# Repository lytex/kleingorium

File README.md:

# Power specs
VCC to GND voltage: 5V to 18V
# Scales generated by it
[kleingorium scale](https://sevish.com/scaleworkshop/?n=kleingorium&l=2F8_3F8_4F8_5F8_6F8_8Fa_7F8_8F9_8F8_9F8_8F7_aF8_8F6_8F5_8F4_8F3_8F2&c=-~~~~~-~-~~-~----&d=6&y=46&version=2.5.7)

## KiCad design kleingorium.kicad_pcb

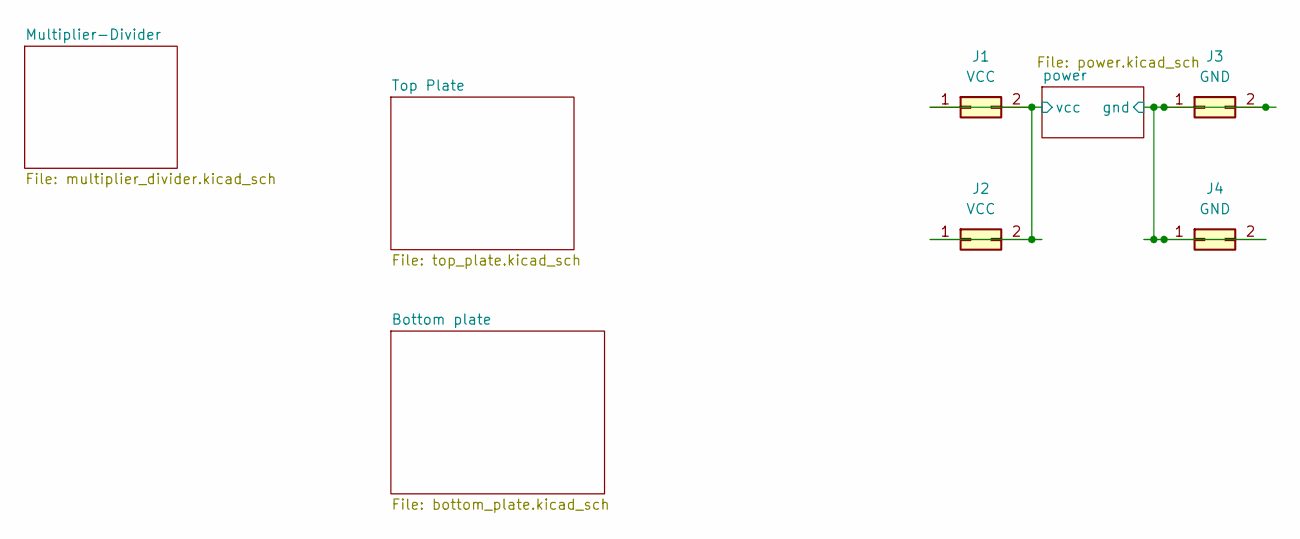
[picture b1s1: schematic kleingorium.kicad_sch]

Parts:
J1, J2: VCC; PinHeader_2x01_P2.54mm_Vertical
J3, J4: GND; PinHeader_2x01_P2.54mm_Vertical

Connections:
GND: J3.1, J3.2, J4.1, J4.2; also elsewhere on the board
VCC: J1.1, J1.2, J2.1, J2.2; also elsewhere on the board

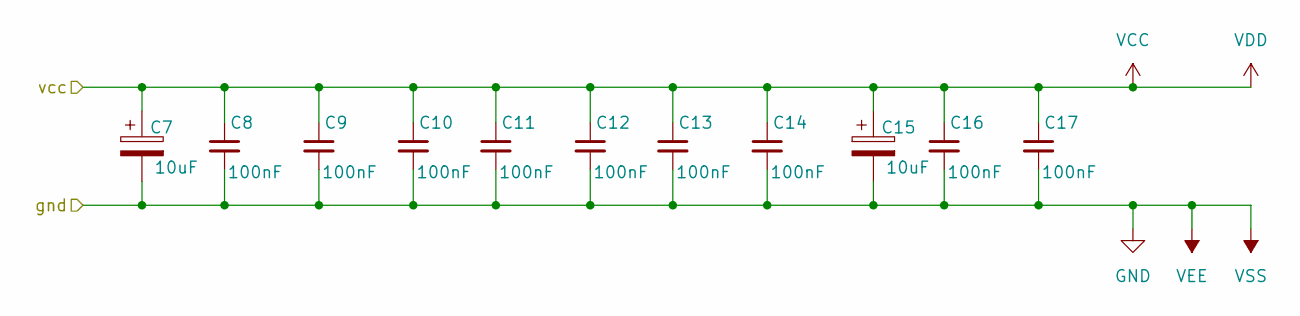
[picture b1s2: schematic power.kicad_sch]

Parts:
C7, C15: 10uF; CP_Radial_D10.0mm_P2.50mm
C8, C9, C10, C11, C12, C13, C14, C16, C17: 100nF; C_0805_2012Metric

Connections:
GND: C7.2, C8.2, C9.2, C10.2, C11.2, C12.2, C13.2, C14.2, C15.2, C16.2, C17.2; also elsewhere on the board
VCC: C7.1, C8.1, C9.1, C10.1, C11.1, C12.1, C13.1, C14.1, C15.1, C16.1, C17.1; also elsewhere on the board

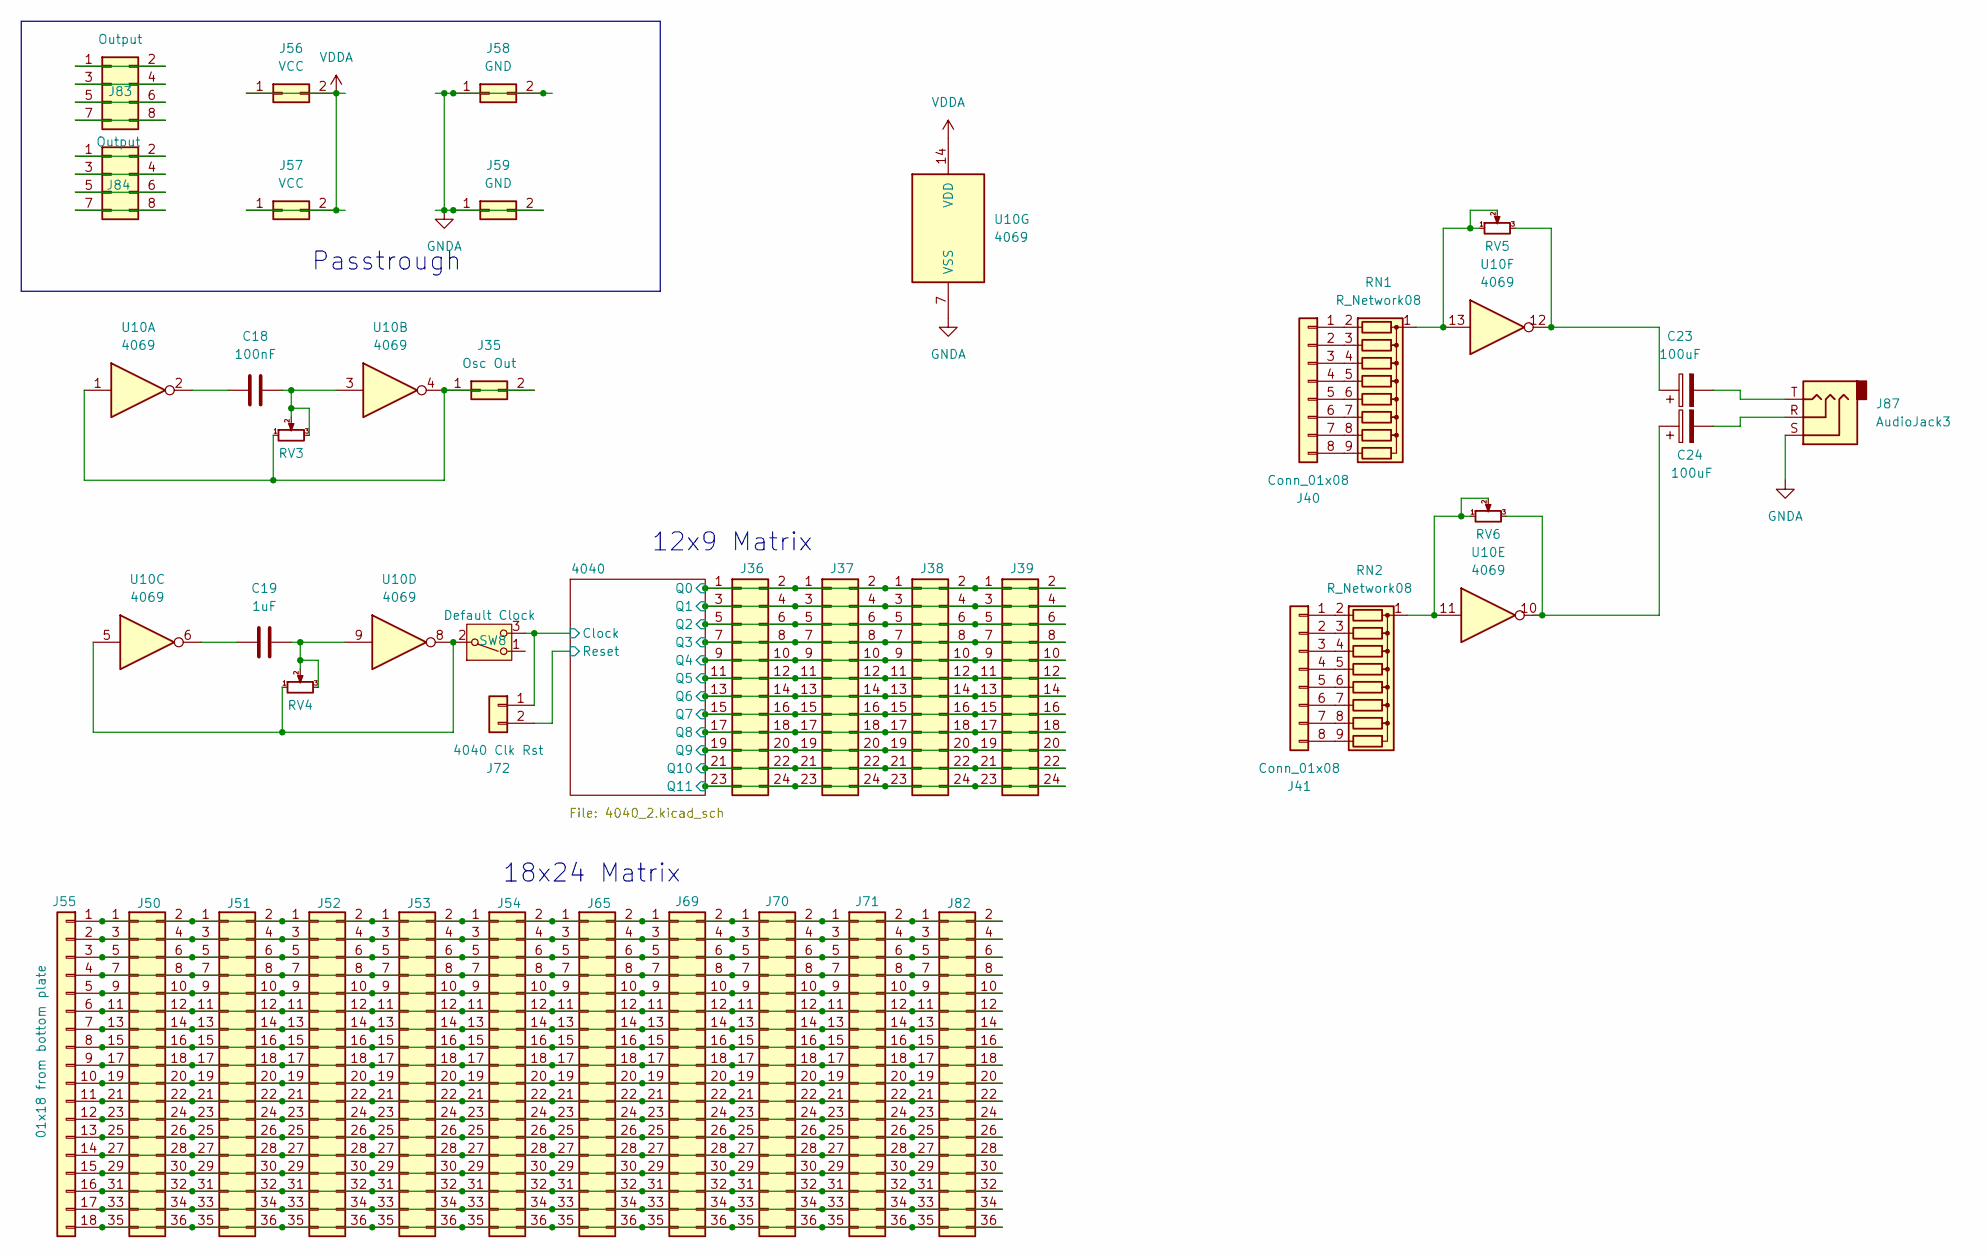
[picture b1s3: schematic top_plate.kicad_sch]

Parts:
C18: 100nF; C_0805_2012Metric
C19: 1uF; C_0805_2012Metric
C23, C24: 100uF; CP_Radial_D10.0mm_P2.50mm
J35: Osc Out; PinHeader_2x01_P2.54mm_Vertical
J36, J37, J38, J39: Conn_02x12_Odd_Even; Header_2x12_P2.54mm_Vertical_SMD_FH-00369
J40, J41: Conn_01x08; PinSocket_1x08_P2.54mm_Vertical
J50, J51, J52, J53, J54, J65, J69, J70, J71, J82: Conn_02x18_Odd_Even; Header_2x18_P2.54mm_Vertical_SMD_FH-00369
J55: 01x18 from bottom plate; PinHeader_1x18_P2.54mm_Vertical
J56, J57: VCC; PinHeader_2x01_P2.54mm_Vertical
J58, J59: GND; PinHeader_2x01_P2.54mm_Vertical
J72: 4040 Clk Rst; PinHeader_1x02_P2.54mm_Vertical
J83, J84: Output; PinHeader_2x04_P2.54mm_Vertical
J87: AudioJack3; Jack_3.5mm_CUI_SJ1-3523N_Horizontal
RN1, RN2: R_Network08; R_Array_SIP9
RV3, RV4, RV5, RV6: R_Potentiometer_Small; Potentiometer_Alps_RK097_Single_Horizontal
SW8: Default Clock; SW_Slide_SPDT_Straight_CK_OS102011MS2Q
U10: 4069; SOIC-14_3.9x8.7mm_P1.27mm

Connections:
/Top Plate/4040/Clock: J72.1, SW8.3 (C); also elsewhere on the board
/Top Plate/4040/Q0: J36.1, J36.2, J37.1, J37.2, J38.1, J38.2, J39.1, J39.2; also elsewhere on the board
/Top Plate/4040/Q1: J36.3, J36.4, J37.3, J37.4, J38.3, J38.4, J39.3, J39.4; also elsewhere on the board
/Top Plate/4040/Q2: J36.5, J36.6, J37.5, J37.6, J38.5, J38.6, J39.5, J39.6; also elsewhere on the board
/Top Plate/4040/Q3: J36.7, J36.8, J37.7, J37.8, J38.7, J38.8, J39.7, J39.8; also elsewhere on the board
/Top Plate/4040/Q4: J36.9, J36.10, J37.9, J37.10, J38.9, J38.10, J39.9, J39.10; also elsewhere on the board
/Top Plate/4040/Q5: J36.11, J36.12, J37.11, J37.12, J38.11, J38.12, J39.11, J39.12; also elsewhere on the board
/Top Plate/4040/Q6: J36.13, J36.14, J37.13, J37.14, J38.13, J38.14, J39.13, J39.14; also elsewhere on the board
/Top Plate/4040/Q7: J36.15, J36.16, J37.15, J37.16, J38.15, J38.16, J39.15, J39.16; also elsewhere on the board
/Top Plate/4040/Q8: J36.17, J36.18, J37.17, J37.18, J38.17, J38.18, J39.17, J39.18; also elsewhere on the board
/Top Plate/4040/Q9: J36.19, J36.20, J37.19, J37.20, J38.19, J38.20, J39.19, J39.20; also elsewhere on the board
/Top Plate/4040/Q10: J36.21, J36.22, J37.21, J37.22, J38.21, J38.22, J39.21, J39.22; also elsewhere on the board
/Top Plate/4040/Q11: J36.23, J36.24, J37.23, J37.24, J38.23, J38.24, J39.23, J39.24; also elsewhere on the board
/Top Plate/4040/Reset: J72.2; also elsewhere on the board
GNDA: J58.1, J58.2, J59.1, J59.2, J87.S, U10.7 (VSS); also elsewhere on the board
unnamed: C18.1, U10.2
unnamed: C18.2, RV3.2, RV3.3, U10.3
unnamed: C19.1, U10.6
unnamed: C19.2, RV4.2, RV4.3, U10.9
unnamed: C23.1, RV5.3, U10.12
unnamed: C23.2, J87.T
unnamed: C24.1, RV6.3, U10.10
unnamed: C24.2, J87.R
unnamed: J35.1, J35.2, RV3.1, U10.1, U10.4
unnamed: J40.1, RN1.2 (R1)
unnamed: J40.2, RN1.3 (R2)
unnamed: J40.3, RN1.4 (R3)
unnamed: J40.4, RN1.5 (R4)
unnamed: J40.5, RN1.6 (R5)
unnamed: J40.6, RN1.7 (R6)
unnamed: J40.7, RN1.8 (R7)
unnamed: J40.8, RN1.9 (R8)
unnamed: J41.1, RN2.2 (R1)
unnamed: J41.2, RN2.3 (R2)
unnamed: J41.3, RN2.4 (R3)
unnamed: J41.4, RN2.5 (R4)
unnamed: J41.5, RN2.6 (R5)
unnamed: J41.6, RN2.7 (R6)
unnamed: J41.7, RN2.8 (R7)
unnamed: J41.8, RN2.9 (R8)
unnamed: J50.1, J50.2, J51.1, J51.2, J52.1, J52.2, J53.1, J53.2, J54.1, J54.2, J55.1, J65.1, J65.2, J69.1, J69.2, J70.1, J70.2, J71.1, J71.2, J82.1, J82.2
unnamed: J50.3, J50.4, J51.3, J51.4, J52.3, J52.4, J53.3, J53.4, J54.3, J54.4, J55.2, J65.3, J65.4, J69.3, J69.4, J70.3, J70.4, J71.3, J71.4, J82.3, J82.4
unnamed: J50.5, J50.6, J51.5, J51.6, J52.5, J52.6, J53.5, J53.6, J54.5, J54.6, J55.3, J65.5, J65.6, J69.5, J69.6, J70.5, J70.6, J71.5, J71.6, J82.5, J82.6
unnamed: J50.7, J50.8, J51.7, J51.8, J52.7, J52.8, J53.7, J53.8, J54.7, J54.8, J55.4, J65.7, J65.8, J69.7, J69.8, J70.7, J70.8, J71.7, J71.8, J82.7, J82.8
unnamed: J50.9, J50.10, J51.9, J51.10, J52.9, J52.10, J53.9, J53.10, J54.9, J54.10, J55.5, J65.9, J65.10, J69.9, J69.10, J70.9, J70.10, J71.9, J71.10, J82.9, J82.10
unnamed: J50.11, J50.12, J51.11, J51.12, J52.11, J52.12, J53.11, J53.12, J54.11, J54.12, J55.6, J65.11, J65.12, J69.11, J69.12, J70.11, J70.12, J71.11, J71.12, J82.11, J82.12
unnamed: J50.13, J50.14, J51.13, J51.14, J52.13, J52.14, J53.13, J53.14, J54.13, J54.14, J55.7, J65.13, J65.14, J69.13, J69.14, J70.13, J70.14, J71.13, J71.14, J82.13, J82.14
unnamed: J50.15, J50.16, J51.15, J51.16, J52.15, J52.16, J53.15, J53.16, J54.15, J54.16, J55.8, J65.15, J65.16, J69.15, J69.16, J70.15, J70.16, J71.15, J71.16, J82.15, J82.16
unnamed: J50.17, J50.18, J51.17, J51.18, J52.17, J52.18, J53.17, J53.18, J54.17, J54.18, J55.9, J65.17, J65.18, J69.17, J69.18, J70.17, J70.18, J71.17, J71.18, J82.17, J82.18
unnamed: J50.19, J50.20, J51.19, J51.20, J52.19, J52.20, J53.19, J53.20, J54.19, J54.20, J55.10, J65.19, J65.20, J69.19, J69.20, J70.19, J70.20, J71.19, J71.20, J82.19, J82.20
unnamed: J50.21, J50.22, J51.21, J51.22, J52.21, J52.22, J53.21, J53.22, J54.21, J54.22, J55.11, J65.21, J65.22, J69.21, J69.22, J70.21, J70.22, J71.21, J71.22, J82.21, J82.22
unnamed: J50.23, J50.24, J51.23, J51.24, J52.23, J52.24, J53.23, J53.24, J54.23, J54.24, J55.12, J65.23, J65.24, J69.23, J69.24, J70.23, J70.24, J71.23, J71.24, J82.23, J82.24
unnamed: J50.25, J50.26, J51.25, J51.26, J52.25, J52.26, J53.25, J53.26, J54.25, J54.26, J55.13, J65.25, J65.26, J69.25, J69.26, J70.25, J70.26, J71.25, J71.26, J82.25, J82.26
unnamed: J50.27, J50.28, J51.27, J51.28, J52.27, J52.28, J53.27, J53.28, J54.27, J54.28, J55.14, J65.27, J65.28, J69.27, J69.28, J70.27, J70.28, J71.27, J71.28, J82.27, J82.28
unnamed: J50.29, J50.30, J51.29, J51.30, J52.29, J52.30, J53.29, J53.30, J54.29, J54.30, J55.15, J65.29, J65.30, J69.29, J69.30, J70.29, J70.30, J71.29, J71.30, J82.29, J82.30
unnamed: J50.31, J50.32, J51.31, J51.32, J52.31, J52.32, J53.31, J53.32, J54.31, J54.32, J55.16, J65.31, J65.32, J69.31, J69.32, J70.31, J70.32, J71.31, J71.32, J82.31, J82.32
unnamed: J50.33, J50.34, J51.33, J51.34, J52.33, J52.34, J53.33, J53.34, J54.33, J54.34, J55.17, J65.33, J65.34, J69.33, J69.34, J70.33, J70.34, J71.33, J71.34, J82.33, J82.34
unnamed: J50.35, J50.36, J51.35, J51.36, J52.35, J52.36, J53.35, J53.36, J54.35, J54.36, J55.18, J65.35, J65.36, J69.35, J69.36, J70.35, J70.36, J71.35, J71.36, J82.35, J82.36
unnamed: J83.1, J83.2
unnamed: J83.3, J83.4
unnamed: J83.5, J83.6
unnamed: J83.7, J83.8
unnamed: J84.1, J84.2
unnamed: J84.3, J84.4
unnamed: J84.5, J84.6
unnamed: J84.7, J84.8
unnamed: RN1.1 (common), RV5.1, RV5.2, U10.13
unnamed: RN2.1 (common), RV6.1, RV6.2, U10.11
unnamed: RV4.1, SW8.2 (B), U10.5, U10.8
VDDA: J56.1, J56.2, J57.1, J57.2, U10.14 (VDD); also elsewhere on the board

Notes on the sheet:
Passtrough
12x9 Matrix
18x24 Matrix

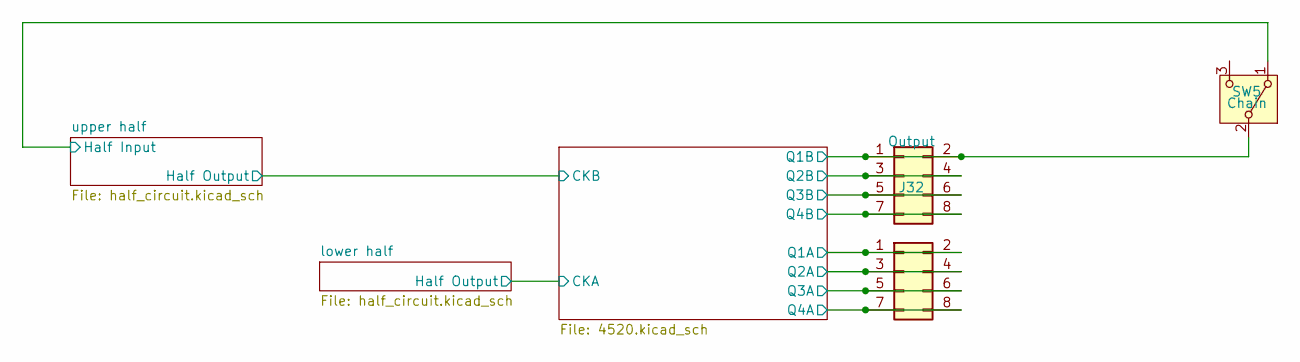
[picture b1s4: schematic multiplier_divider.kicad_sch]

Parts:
J31, J32: Output; PinHeader_2x04_P2.54mm_Vertical
SW5: Chain; SW_Slide_SPDT_Straight_CK_OS102011MS2Q

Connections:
/Multiplier-Divider/4520/Q1A: J31.1, J31.2; also elsewhere on the board
/Multiplier-Divider/4520/Q1B: J32.1, J32.2, SW5.2 (B); also elsewhere on the board
/Multiplier-Divider/4520/Q2A: J31.3, J31.4; also elsewhere on the board
/Multiplier-Divider/4520/Q2B: J32.3, J32.4; also elsewhere on the board
/Multiplier-Divider/4520/Q3A: J31.5, J31.6; also elsewhere on the board
/Multiplier-Divider/4520/Q3B: J32.5, J32.6; also elsewhere on the board
/Multiplier-Divider/4520/Q4A: J31.7, J31.8; also elsewhere on the board
/Multiplier-Divider/4520/Q4B: J32.7, J32.8; also elsewhere on the board
/Multiplier-Divider/upper half/Half Input: SW5.1 (A); also elsewhere on the board

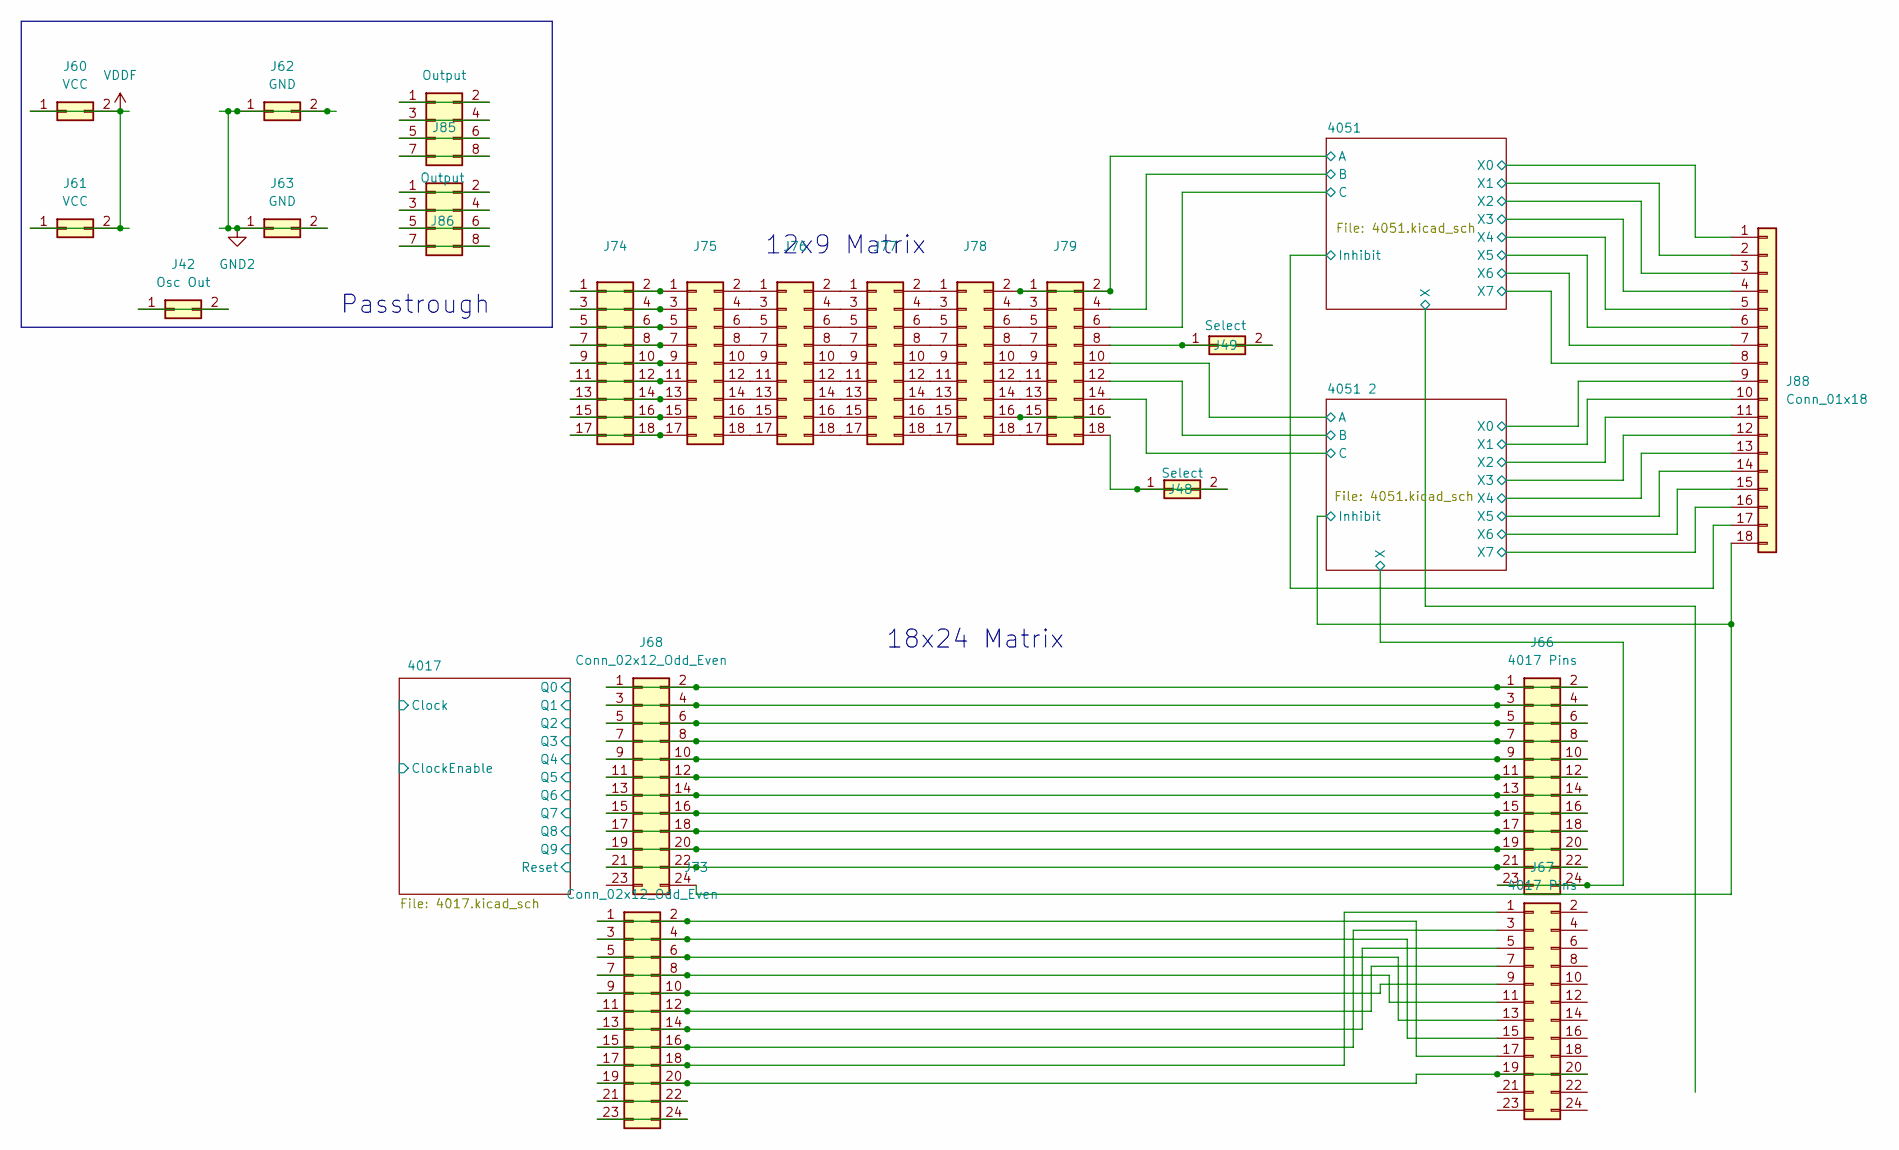
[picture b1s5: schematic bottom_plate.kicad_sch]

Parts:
J42: Osc Out; PinHeader_2x01_P2.54mm_Vertical
J48, J49: Select; PinHeader_2x01_P2.54mm_Vertical
J60, J61: VCC; PinHeader_2x01_P2.54mm_Vertical
J62, J63: GND; PinHeader_2x01_P2.54mm_Vertical
J66, J67: 4017 Pins; PinSocket_2x12_P2.54mm_Vertical
J68, J73: Conn_02x12_Odd_Even; Header_2x12_P2.54mm_Vertical_SMD_FH-00369
J74, J75, J76, J77, J78, J79: Conn_02x09_Odd_Even; PinHeader_2x09_P2.54mm_Vertical
J85, J86: Output; PinHeader_2x04_P2.54mm_Vertical
J88: Conn_01x18; PinHeader_1x18_P2.54mm_Vertical

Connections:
/Bottom plate/4051 2/A: J79.10; also elsewhere on the board
/Bottom plate/4051 2/B: J79.12; also elsewhere on the board
/Bottom plate/4051 2/C: J79.14; also elsewhere on the board
/Bottom plate/4051 2/Inhibit: J68.24, J88.18; also elsewhere on the board
/Bottom plate/4051 2/X: J66.23, J66.24; also elsewhere on the board
/Bottom plate/4051 2/X0: J88.9; also elsewhere on the board
/Bottom plate/4051 2/X1: J88.10; also elsewhere on the board
/Bottom plate/4051 2/X2: J88.11; also elsewhere on the board
/Bottom plate/4051 2/X3: J88.12; also elsewhere on the board
/Bottom plate/4051 2/X4: J88.13; also elsewhere on the board
/Bottom plate/4051 2/X5: J88.14; also elsewhere on the board
/Bottom plate/4051 2/X6: J88.15; also elsewhere on the board
/Bottom plate/4051 2/X7: J88.16; also elsewhere on the board
/Bottom plate/4051/A: J78.2, J79.1, J79.2; also elsewhere on the board
/Bottom plate/4051/B: J79.4; also elsewhere on the board
/Bottom plate/4051/C: J79.6; also elsewhere on the board
/Bottom plate/4051/Inhibit: J88.17; also elsewhere on the board
/Bottom plate/4051/X0: J88.1; also elsewhere on the board
/Bottom plate/4051/X1: J88.2; also elsewhere on the board
/Bottom plate/4051/X2: J88.3; also elsewhere on the board
/Bottom plate/4051/X3: J88.4; also elsewhere on the board
/Bottom plate/4051/X4: J88.5; also elsewhere on the board
/Bottom plate/4051/X5: J88.6; also elsewhere on the board
/Bottom plate/4051/X6: J88.7; also elsewhere on the board
/Bottom plate/4051/X7: J88.8; also elsewhere on the board
GND2: J62.1, J62.2, J63.1, J63.2; also elsewhere on the board
unnamed: J42.1, J42.2
unnamed: J48.1, J48.2, J79.18
unnamed: J49.1, J49.2, J79.8
unnamed: J66.1, J66.2, J68.1, J68.2
unnamed: J66.3, J66.4, J68.3, J68.4
unnamed: J66.5, J66.6, J68.5, J68.6
unnamed: J66.7, J66.8, J68.7, J68.8
unnamed: J66.9, J66.10, J68.9, J68.10
unnamed: J66.11, J66.12, J68.11, J68.12
unnamed: J66.13, J66.14, J68.13, J68.14
unnamed: J66.15, J66.16, J68.15, J68.16
unnamed: J66.17, J66.18, J68.17, J68.18
unnamed: J66.19, J66.20, J68.19, J68.20
unnamed: J66.21, J66.22, J68.21, J68.22
unnamed: J67.1, J73.17, J73.18
unnamed: J67.3, J73.15, J73.16
unnamed: J67.5, J73.13, J73.14
unnamed: J67.7, J73.11, J73.12
unnamed: J67.9, J73.9, J73.10
unnamed: J67.11, J73.7, J73.8
unnamed: J67.13, J73.5, J73.6
unnamed: J67.15, J73.3, J73.4
unnamed: J67.17, J73.1, J73.2
unnamed: J67.19, J67.20, J73.19, J73.20
unnamed: J73.21, J73.22
unnamed: J73.23, J73.24
unnamed: J74.1, J74.2, J75.1
unnamed: J74.3, J74.4, J75.3
unnamed: J74.5, J74.6, J75.5
unnamed: J74.7, J74.8, J75.7
unnamed: J74.9, J74.10, J75.9
unnamed: J74.11, J74.12, J75.11
unnamed: J74.13, J74.14, J75.13
unnamed: J74.15, J74.16, J75.15
unnamed: J74.17, J74.18, J75.17
unnamed: J75.2, J76.1
unnamed: J75.4, J76.3
unnamed: J75.6, J76.5
unnamed: J75.8, J76.7
unnamed: J75.10, J76.9
unnamed: J75.12, J76.11
unnamed: J75.14, J76.13
unnamed: J75.16, J76.15
unnamed: J75.18, J76.17
unnamed: J76.2, J77.1
unnamed: J76.4, J77.3
unnamed: J76.6, J77.5
unnamed: J76.8, J77.7
unnamed: J76.10, J77.9
unnamed: J76.12, J77.11
unnamed: J76.14, J77.13
unnamed: J76.16, J77.15
unnamed: J76.18, J77.17
unnamed: J77.2, J78.1
unnamed: J77.4, J78.3
unnamed: J77.6, J78.5
unnamed: J77.8, J78.7
unnamed: J77.10, J78.9
unnamed: J77.12, J78.11
unnamed: J77.14, J78.13
unnamed: J77.16, J78.15
unnamed: J77.18, J78.17
unnamed: J78.4, J79.3
unnamed: J78.6, J79.5
unnamed: J78.8, J79.7
unnamed: J78.10, J79.9
unnamed: J78.12, J79.11
unnamed: J78.14, J79.13
unnamed: J78.16, J79.15, J79.16
unnamed: J78.18, J79.17
unnamed: J85.1, J85.2
unnamed: J85.3, J85.4
unnamed: J85.5, J85.6
unnamed: J85.7, J85.8
unnamed: J86.1, J86.2
unnamed: J86.3, J86.4
unnamed: J86.5, J86.6
unnamed: J86.7, J86.8
VDDF: J60.1, J60.2, J61.1, J61.2; also elsewhere on the board

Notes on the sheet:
Passtrough
18x24 Matrix
12x9 Matrix

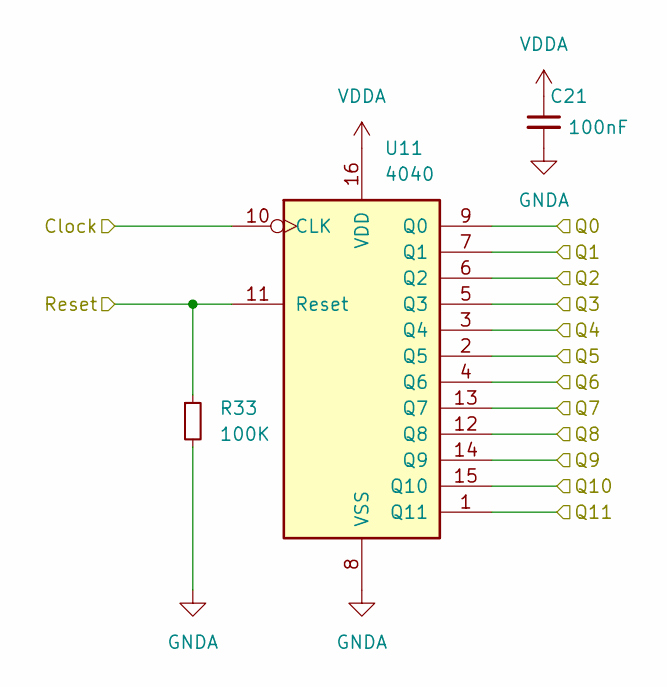
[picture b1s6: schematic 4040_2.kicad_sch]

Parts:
C21: 100nF; C_0805_2012Metric
R33: 100K; R_0805_2012Metric
U11: 4040; SOIC-16_3.9x9.9mm_P1.27mm

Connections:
/Top Plate/4040/Clock: U11.10 (CLK); also elsewhere on the board
/Top Plate/4040/Q0: U11.9 (Q0); also elsewhere on the board
/Top Plate/4040/Q1: U11.7 (Q1); also elsewhere on the board
/Top Plate/4040/Q2: U11.6 (Q2); also elsewhere on the board
/Top Plate/4040/Q3: U11.5 (Q3); also elsewhere on the board
/Top Plate/4040/Q4: U11.3 (Q4); also elsewhere on the board
/Top Plate/4040/Q5: U11.2 (Q5); also elsewhere on the board
/Top Plate/4040/Q6: U11.4 (Q6); also elsewhere on the board
/Top Plate/4040/Q7: U11.13 (Q7); also elsewhere on the board
/Top Plate/4040/Q8: U11.12 (Q8); also elsewhere on the board
/Top Plate/4040/Q9: U11.14 (Q9); also elsewhere on the board
/Top Plate/4040/Q10: U11.15 (Q10); also elsewhere on the board
/Top Plate/4040/Q11: U11.1 (Q11); also elsewhere on the board
/Top Plate/4040/Reset: R33.1, U11.11 (Reset); also elsewhere on the board
GNDA: C21.2, R33.2, U11.8 (VSS); also elsewhere on the board
VDDA: C21.1, U11.16 (VDD); also elsewhere on the board

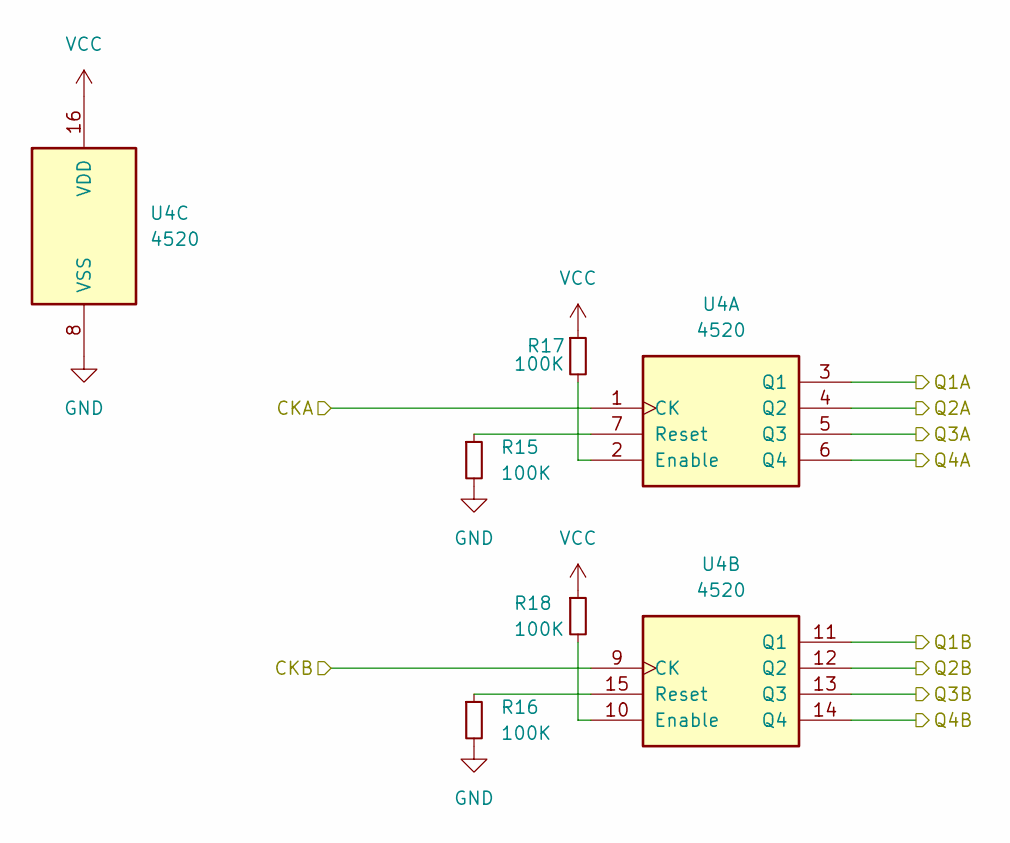
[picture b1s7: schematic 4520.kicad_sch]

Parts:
R15, R16, R17, R18: 100K; R_0805_2012Metric
U4: 4520; SOIC-16_3.9x9.9mm_P1.27mm

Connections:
/Multiplier-Divider/4520/CKA: U4.1 (CK); also elsewhere on the board
/Multiplier-Divider/4520/CKB: U4.9 (CK); also elsewhere on the board
/Multiplier-Divider/4520/Q1A: U4.3 (Q1); also elsewhere on the board
/Multiplier-Divider/4520/Q1B: U4.11 (Q1); also elsewhere on the board
/Multiplier-Divider/4520/Q2A: U4.4 (Q2); also elsewhere on the board
/Multiplier-Divider/4520/Q2B: U4.12 (Q2); also elsewhere on the board
/Multiplier-Divider/4520/Q3A: U4.5 (Q3); also elsewhere on the board
/Multiplier-Divider/4520/Q3B: U4.13 (Q3); also elsewhere on the board
/Multiplier-Divider/4520/Q4A: U4.6 (Q4); also elsewhere on the board
/Multiplier-Divider/4520/Q4B: U4.14 (Q4); also elsewhere on the board
GND: R15.2, R16.2, U4.8 (VSS); also elsewhere on the board
unnamed: R17.2, U4.2 (Enable)
unnamed: R15.1, U4.7 (Reset)
unnamed: R18.2, U4.10 (Enable)
unnamed: R16.1, U4.15 (Reset)
VCC: R17.1, R18.1, U4.16 (VDD); also elsewhere on the board

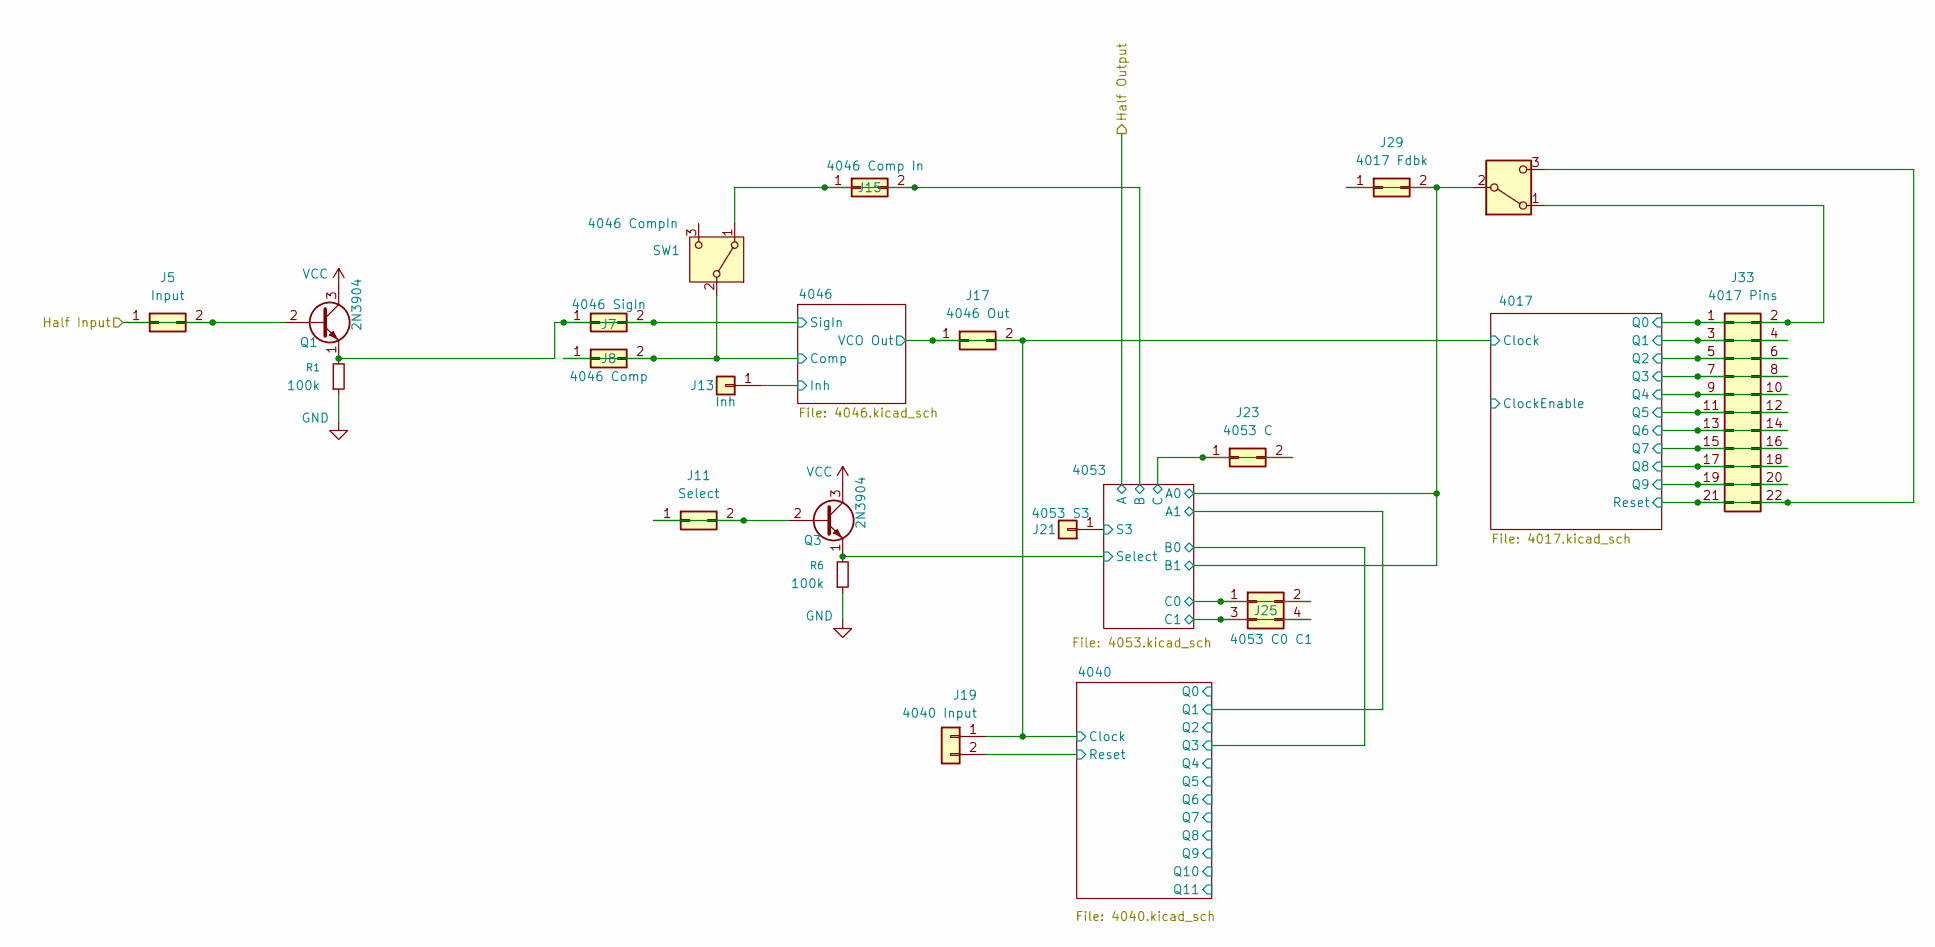
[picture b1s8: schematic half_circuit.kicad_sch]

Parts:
J5: Input; PinHeader_2x01_P2.54mm_Vertical
J7: 4046 SigIn; PinHeader_2x01_P2.54mm_Vertical
J8: 4046 Comp; PinHeader_2x01_P2.54mm_Vertical
J11: Select; PinHeader_2x01_P2.54mm_Vertical
J13: Inh; PinHeader_1x01_P2.54mm_Vertical
J15: 4046 Comp In; PinHeader_2x01_P2.54mm_Vertical
J17: 4046 Out; PinHeader_2x01_P2.54mm_Vertical
J19: 4040 Input; PinHeader_1x02_P2.54mm_Vertical
J21: 4053 S3; PinHeader_1x01_P2.54mm_Vertical
J23: 4053 C; PinHeader_2x01_P2.54mm_Vertical
J25: 4053 C0 C1; PinHeader_2x02_P2.54mm_Vertical
J29: 4017 Fdbk; PinHeader_2x01_P2.54mm_Vertical
J33: 4017 Pins; PinSocket_2x11_P2.54mm_Vertical
Q1, Q3: 2N3904; SOT-23
R1, R6: 100k; R_0805_2012Metric
SW1: 4046 CompIn; SW_Slide_SPDT_Straight_CK_OS102011MS2Q
SW3: 4017 Feedback; SW_Slide_SPDT_Straight_CK_OS102011MS2Q

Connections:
/Multiplier-Divider/upper half/4017/Clock: J17.1, J17.2, J19.1; also elsewhere on the board
/Multiplier-Divider/upper half/4017/Q0: J33.1, J33.2, SW3.1 (A); also elsewhere on the board
/Multiplier-Divider/upper half/4017/Q1: J33.3, J33.4; also elsewhere on the board
/Multiplier-Divider/upper half/4017/Q2: J33.5, J33.6; also elsewhere on the board
/Multiplier-Divider/upper half/4017/Q3: J33.7, J33.8; also elsewhere on the board
/Multiplier-Divider/upper half/4017/Q4: J33.9, J33.10; also elsewhere on the board
/Multiplier-Divider/upper half/4017/Q5: J33.11, J33.12; also elsewhere on the board
/Multiplier-Divider/upper half/4017/Q6: J33.13, J33.14; also elsewhere on the board
/Multiplier-Divider/upper half/4017/Q7: J33.15, J33.16; also elsewhere on the board
/Multiplier-Divider/upper half/4017/Q8: J33.17, J33.18; also elsewhere on the board
/Multiplier-Divider/upper half/4017/Q9: J33.19, J33.20; also elsewhere on the board
/Multiplier-Divider/upper half/4017/Reset: J33.21, J33.22, SW3.3 (C); also elsewhere on the board
/Multiplier-Divider/upper half/4040/Reset: J19.2; also elsewhere on the board
/Multiplier-Divider/upper half/4046/Comp: J8.1, J8.2, SW1.2 (B); also elsewhere on the board
/Multiplier-Divider/upper half/4046/Inh: J13.1 (Pin_1_1); also elsewhere on the board
/Multiplier-Divider/upper half/4046/SigIn: J7.1, J7.2, Q1.1 (E), R1.2; also elsewhere on the board
/Multiplier-Divider/upper half/4053/A0: J29.1, J29.2, SW3.2 (B); also elsewhere on the board
/Multiplier-Divider/upper half/4053/B: J15.1, J15.2, SW1.1 (A); also elsewhere on the board
/Multiplier-Divider/upper half/4053/C: J23.1, J23.2; also elsewhere on the board
/Multiplier-Divider/upper half/4053/C0: J25.1, J25.2; also elsewhere on the board
/Multiplier-Divider/upper half/4053/C1: J25.3, J25.4; also elsewhere on the board
/Multiplier-Divider/upper half/4053/S3: J21.1 (Pin_1_1); also elsewhere on the board
/Multiplier-Divider/upper half/4053/Select: Q3.1 (E), R6.2; also elsewhere on the board
/Multiplier-Divider/upper half/Half Input: J5.1, J5.2, Q1.2 (B); also elsewhere on the board
GND: R1.1, R6.1; also elsewhere on the board
unnamed: J11.1, J11.2, Q3.2 (B)
VCC: Q1.3 (C), Q3.3 (C); also elsewhere on the board

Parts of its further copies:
J6: Input; PinHeader_2x01_P2.54mm_Vertical
J9: 4046 SigIn; PinHeader_2x01_P2.54mm_Vertical
J10: 4046 Comp; PinHeader_2x01_P2.54mm_Vertical
J12: Select; PinHeader_2x01_P2.54mm_Vertical
J14: Inh; PinHeader_1x01_P2.54mm_Vertical
J16: 4046 Comp In; PinHeader_2x01_P2.54mm_Vertical
J18: 4046 Out; PinHeader_2x01_P2.54mm_Vertical
J20: 4040 Input; PinHeader_1x02_P2.54mm_Vertical
J22: 4053 S3; PinHeader_1x01_P2.54mm_Vertical
J24: 4053 C; PinHeader_2x01_P2.54mm_Vertical
J26: 4053 C0 C1; PinHeader_2x02_P2.54mm_Vertical
J30: 4017 Fdbk; PinHeader_2x01_P2.54mm_Vertical
J34: 4017 Pins; PinSocket_2x11_P2.54mm_Vertical
Q2, Q4: 2N3904; SOT-23
R31, R32: 100k; R_0805_2012Metric
SW4: 4017 Feedback; SW_Slide_SPDT_Straight_CK_OS102011MS2Q
SW7: 4046 CompIn; SW_Slide_SPDT_Straight_CK_OS102011MS2Q

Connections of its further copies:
/Multiplier-Divider/lower half/4017/Clock: J18.1, J18.2, J20.1; also elsewhere on the board
/Multiplier-Divider/lower half/4017/Q0: J34.1, J34.2, SW4.1 (A); also elsewhere on the board
/Multiplier-Divider/lower half/4017/Q1: J34.3, J34.4; also elsewhere on the board
/Multiplier-Divider/lower half/4017/Q2: J34.5, J34.6; also elsewhere on the board
/Multiplier-Divider/lower half/4017/Q3: J34.7, J34.8; also elsewhere on the board
/Multiplier-Divider/lower half/4017/Q4: J34.9, J34.10; also elsewhere on the board
/Multiplier-Divider/lower half/4017/Q5: J34.11, J34.12; also elsewhere on the board
/Multiplier-Divider/lower half/4017/Q6: J34.13, J34.14; also elsewhere on the board
/Multiplier-Divider/lower half/4017/Q7: J34.15, J34.16; also elsewhere on the board
/Multiplier-Divider/lower half/4017/Q8: J34.17, J34.18; also elsewhere on the board
/Multiplier-Divider/lower half/4017/Q9: J34.19, J34.20; also elsewhere on the board
/Multiplier-Divider/lower half/4017/Reset: J34.21, J34.22, SW4.3 (C); also elsewhere on the board
/Multiplier-Divider/lower half/4040/Reset: J20.2; also elsewhere on the board
/Multiplier-Divider/lower half/4046/Comp: J10.1, J10.2, SW7.2 (B); also elsewhere on the board
/Multiplier-Divider/lower half/4046/Inh: J14.1 (Pin_1_1); also elsewhere on the board
/Multiplier-Divider/lower half/4046/SigIn: J9.1, J9.2, Q2.1 (E), R31.2; also elsewhere on the board
/Multiplier-Divider/lower half/4053/A0: J30.1, J30.2, SW4.2 (B); also elsewhere on the board
/Multiplier-Divider/lower half/4053/B: J16.1, J16.2, SW7.1 (A); also elsewhere on the board
/Multiplier-Divider/lower half/4053/C: J24.1, J24.2; also elsewhere on the board
/Multiplier-Divider/lower half/4053/C0: J26.1, J26.2; also elsewhere on the board
/Multiplier-Divider/lower half/4053/C1: J26.3, J26.4; also elsewhere on the board
/Multiplier-Divider/lower half/4053/S3: J22.1 (Pin_1_1); also elsewhere on the board
/Multiplier-Divider/lower half/4053/Select: Q4.1 (E), R32.2; also elsewhere on the board
/Multiplier-Divider/lower half/Half Input: J6.1, J6.2, Q2.2 (B)
GND: R31.1, R32.1; also elsewhere on the board
unnamed: J12.1, J12.2, Q4.2 (B)
VCC: Q2.3 (C), Q4.3 (C); also elsewhere on the board
